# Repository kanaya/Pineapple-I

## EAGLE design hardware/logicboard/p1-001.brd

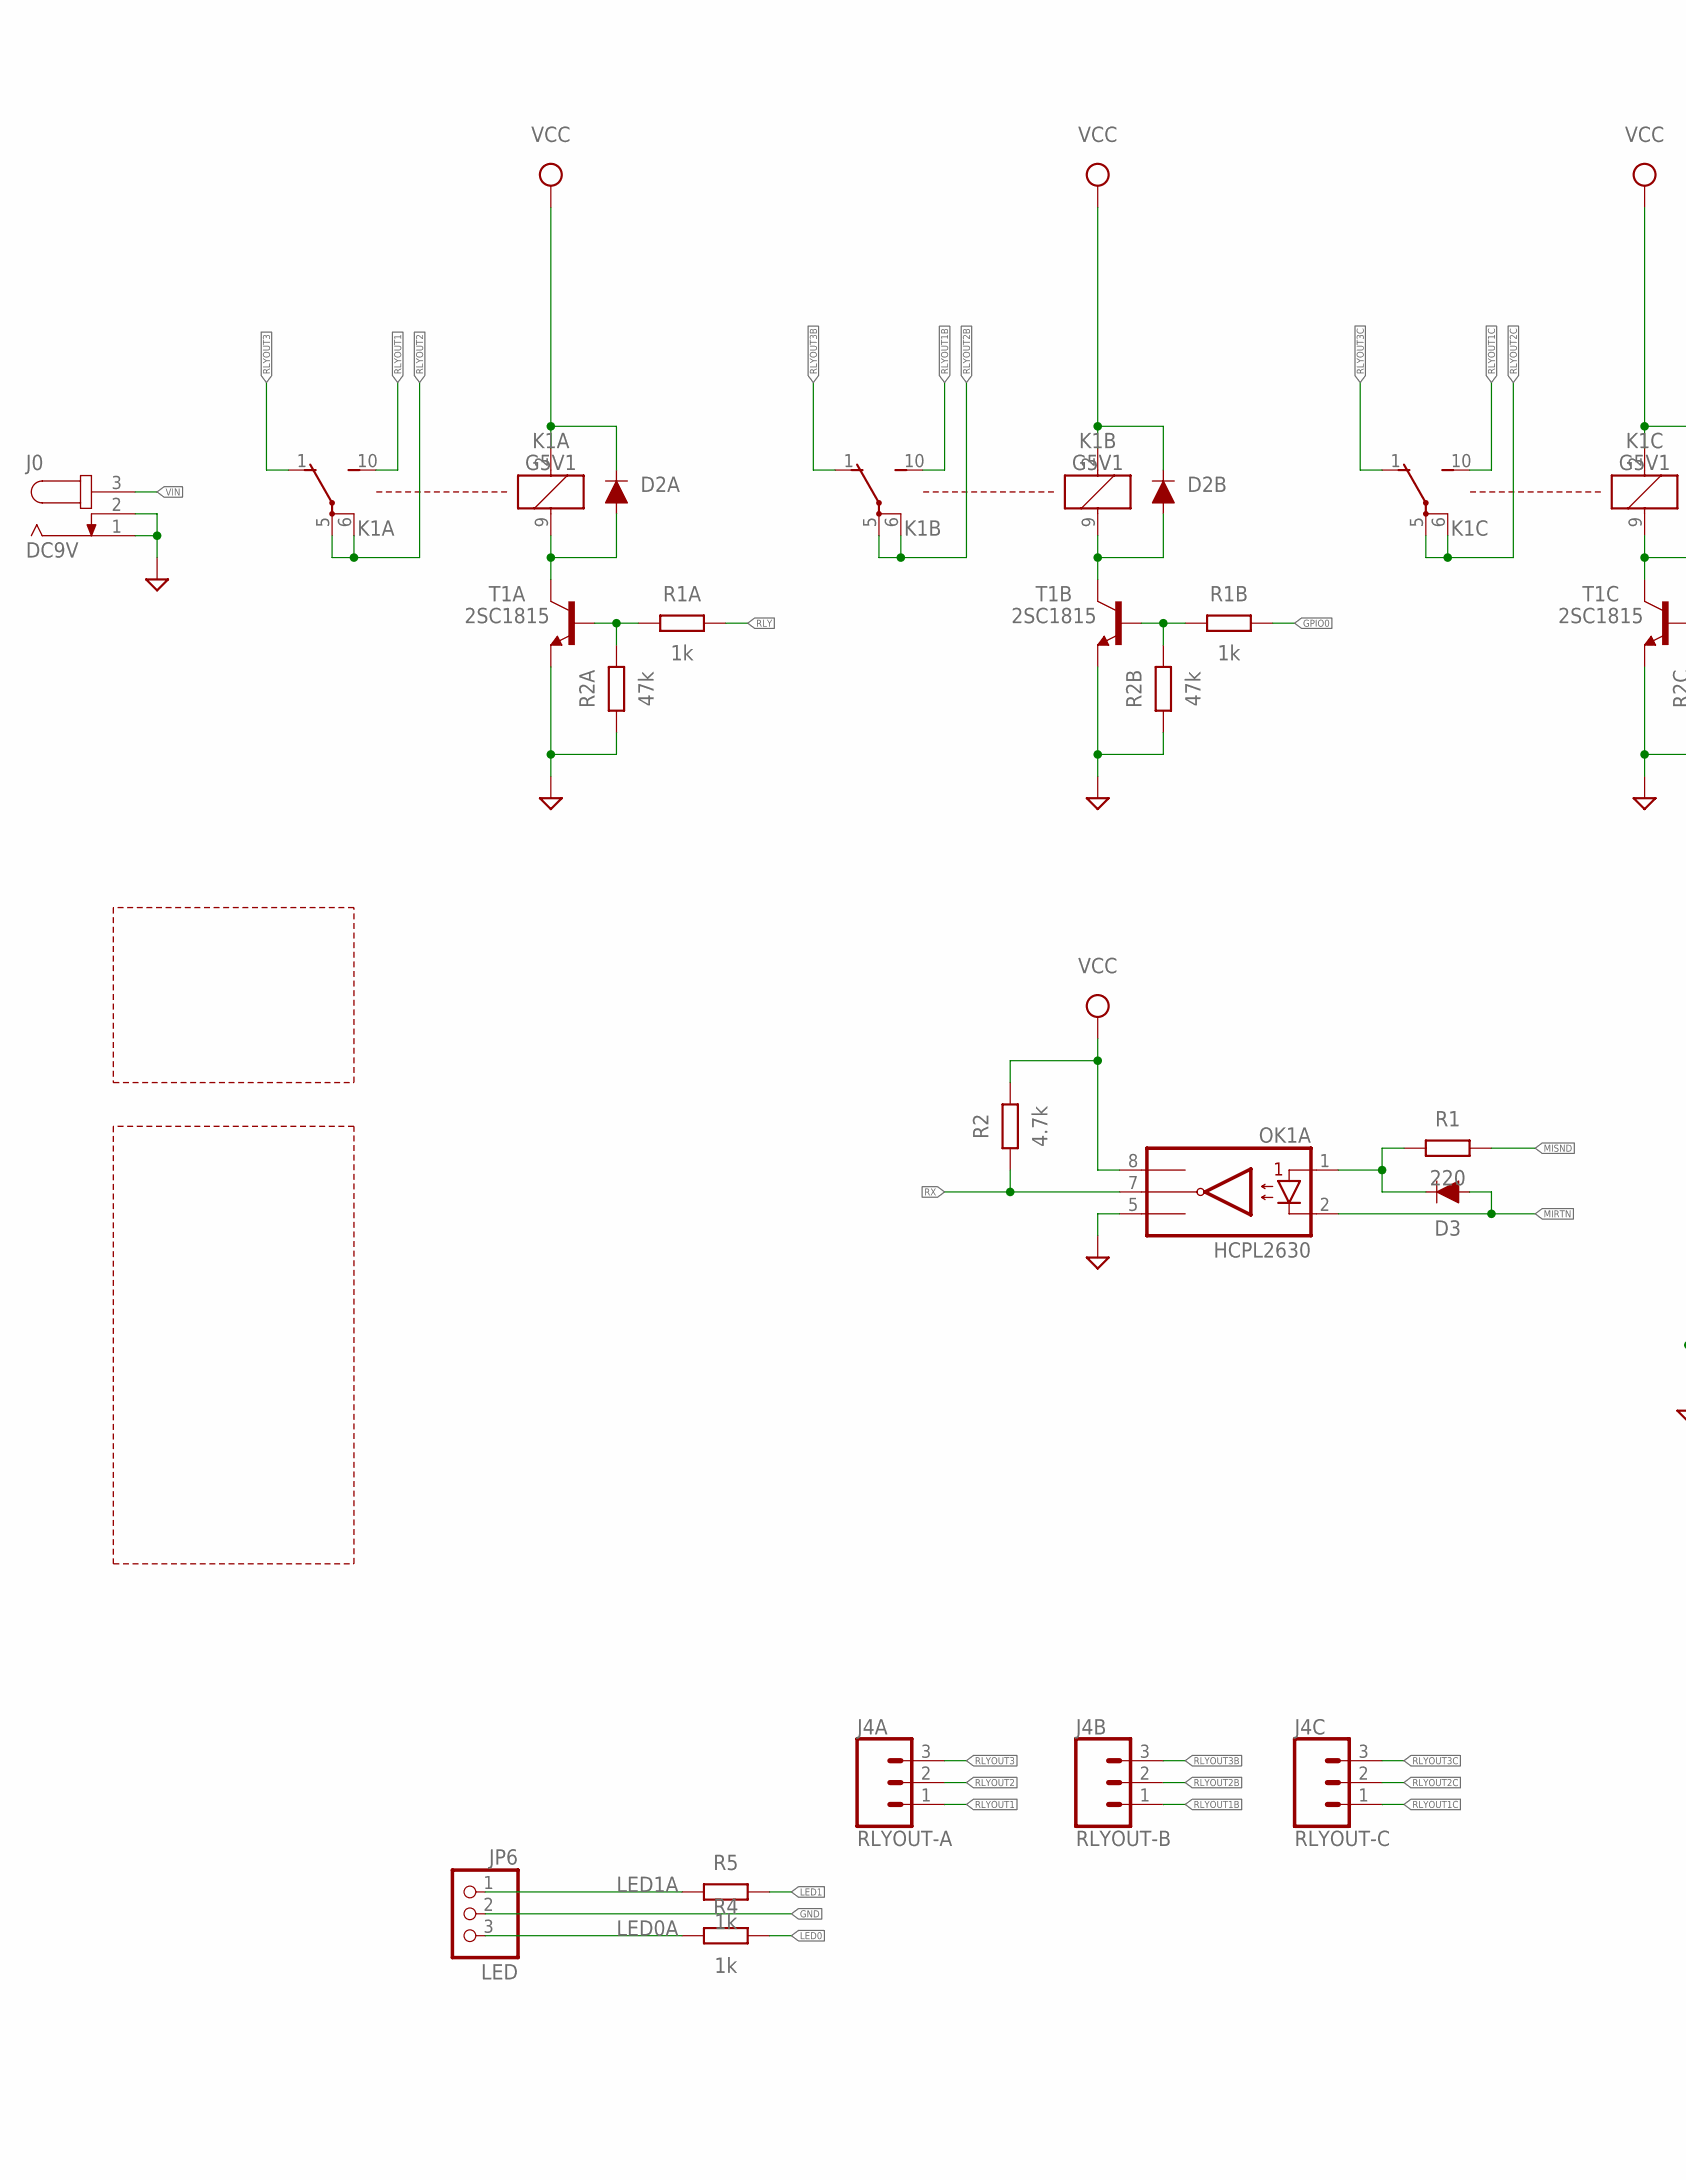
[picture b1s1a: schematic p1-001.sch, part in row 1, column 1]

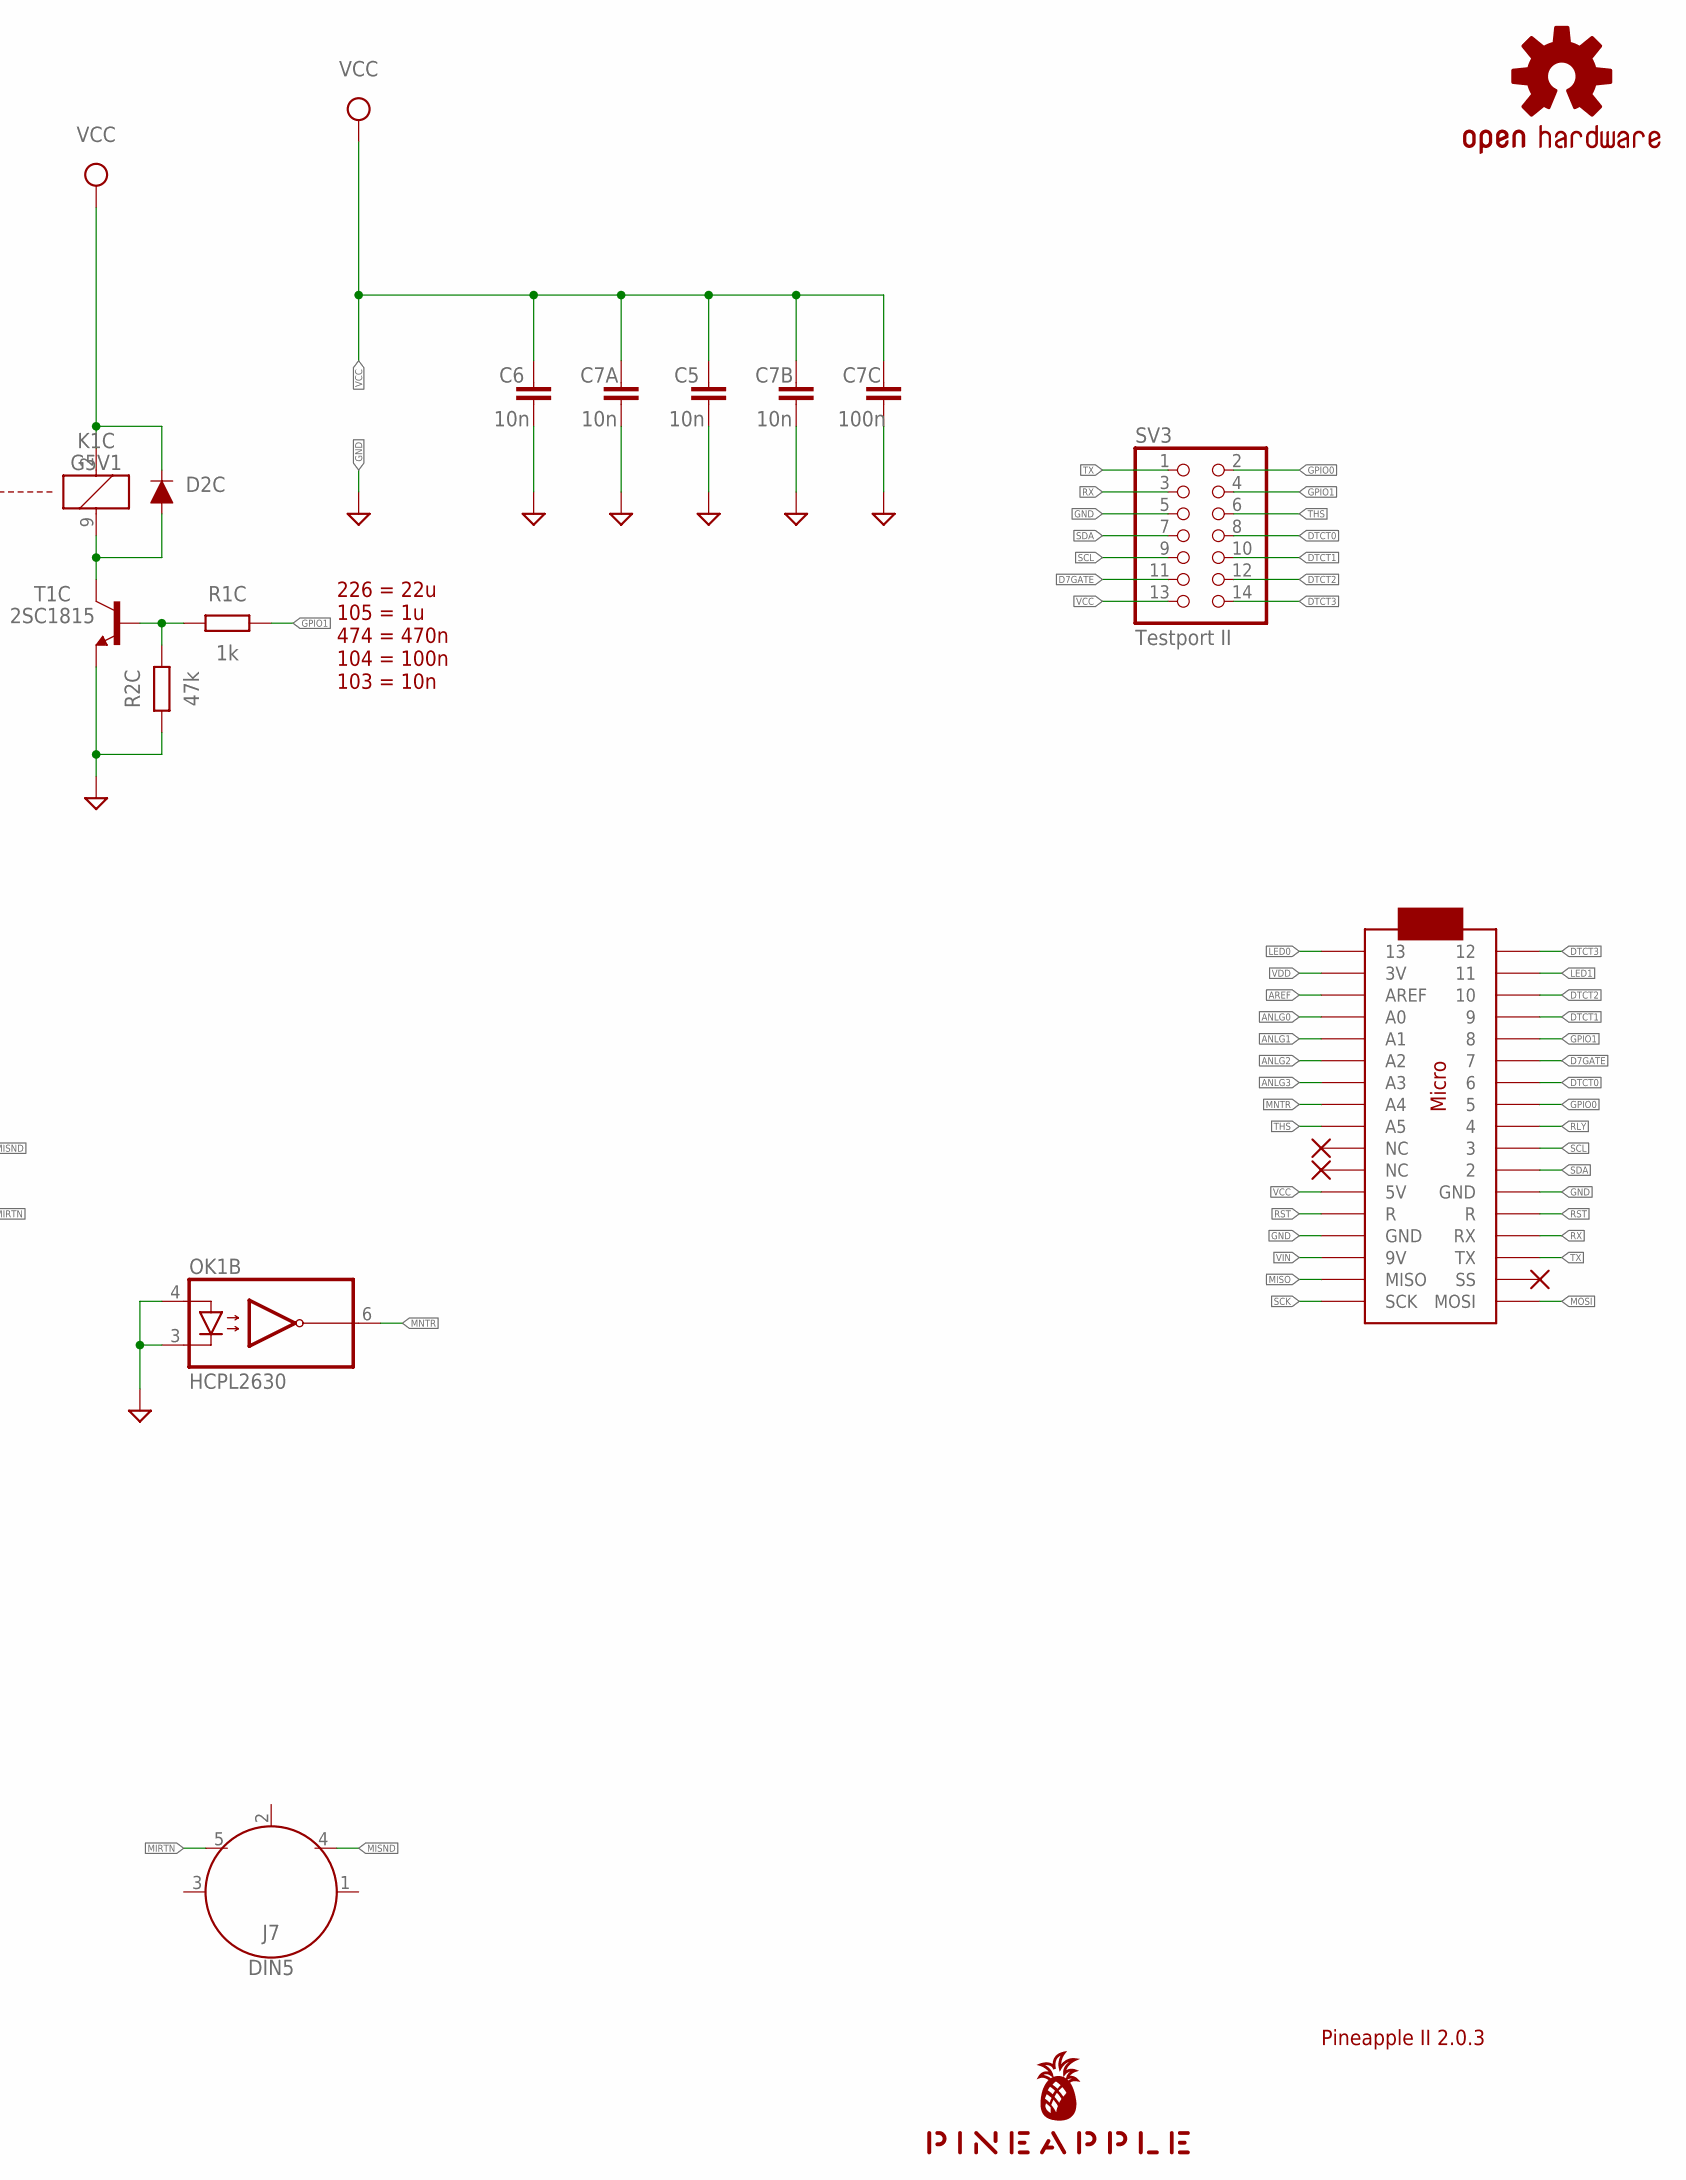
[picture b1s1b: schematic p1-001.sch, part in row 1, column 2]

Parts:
C5, C6, C7A, C7B: 10n; C025-024X044
C7C: 100n; C025-024X044
D2A, D2B, D2C, D3: DIODE-1N4148
J0: DC9V; SPC4077
J4A: RLYOUT-A; JST-3-PTH
J4B: RLYOUT-B; JST-3-PTH
J4C: RLYOUT-C; JST-3-PTH
J7: DIN5; DIN5-RA-PTH
JP6: LED; 1X03
K1A, K1B, K1C: G5V1
LOGO1: OSHW-LOGOS-COPPER; OSHW-LOGO-S_COPPER
MC1: ARDUINOMICRO
OK1: HCPL2630; DIL08
R1: 220; 0204/5
R1A, R1B, R1C, R4, R5: 1k; 0204/5
R2: 4.7k; 0204/5
R2A, R2B, R2C: 47k; 0204/5
SV3: Testport II; 2X07
T1A, T1B, T1C: 2SC1815; TO92-ECB
U$1: PINEAPPLE450_SILK

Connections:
ANLG0: MC1.P$31 (A0)
ANLG1: MC1.P$30 (A1)
ANLG2: MC1.P$29 (A2)
ANLG3: MC1.P$28 (A3)
AREF: MC1.P$32 (AREF)
D7GATE: MC1.P$6 (7), SV3.11; also elsewhere on the board
DTCT0: MC1.P$7 (6), SV3.8
DTCT1: MC1.P$4 (9), SV3.10
DTCT2: MC1.P$3 (10), SV3.12
DTCT3: MC1.P$1 (12), SV3.14
GND: C5.2, C6.2, C7A.2, C7B.2, C7C.2, J0.1, J0.2, JP6.2, MC1.P$12 (GND), MC1.P$21 (GND), OK1.3 (C2), OK1.4 (A2), OK1.5 (GND), R2A.1, R2B.1, R2C.1, SV3.5, T1A.E, T1B.E, T1C.E; also elsewhere on the board
GPIO0: MC1.P$8 (5), R1B.2, SV3.2; also elsewhere on the board
GPIO1: MC1.P$5 (8), R1C.2, SV3.4; also elsewhere on the board
LED0: MC1.P$34 (13), R4.2
LED0A: JP6.3, R4.1
LED1: MC1.P$2 (11), R5.2
LED1A: JP6.1, R5.1
MIDIINSND: D3.C, OK1.1 (A1), R1.1
MIRTN: D3.A, J7.5, OK1.2 (C1)
MISND: J7.4, R1.2
MISO: MC1.P$19 (MISO); also elsewhere on the board
MNTR: MC1.P$27 (A4), OK1.6 (VO2)
MOSI: MC1.P$17 (MOSI); also elsewhere on the board
RLY: MC1.P$9 (4), R1A.2
RLYDRV: R1A.1, R2A.2, T1A.B
RLYDRV1: R1B.1, R2B.2, T1B.B
RLYDRV2: R1C.1, R2C.2, T1C.B
RLYOUT1: J4A.1, K1A.10 (S)
RLYOUT1B: J4B.1, K1B.10 (S)
RLYOUT1C: J4C.1, K1C.10 (S)
RLYOUT2: J4A.2, K1A.5, K1A.6
RLYOUT2B: J4B.2, K1B.5, K1B.6
RLYOUT2C: J4C.2, K1C.5, K1C.6
RLYOUT3: J4A.3, K1A.1 (O)
RLYOUT3B: J4B.3, K1B.1 (O)
RLYOUT3C: J4C.3, K1C.1 (O)
RLYSNK: D2A.A, K1A.9 (2), T1A.C
RLYSNK1: D2B.A, K1B.9 (2), T1B.C
RLYSNK2: D2C.A, K1C.9 (2), T1C.C
RST: MC1.P$13 (R), MC1.P$22 (R); also elsewhere on the board
RX: MC1.P$14 (RX), OK1.7 (VO1), R2.1, SV3.3
SCK: MC1.P$18 (SCK); also elsewhere on the board
SCL: MC1.P$10 (3), SV3.9; also elsewhere on the board
SDA: MC1.P$11 (2), SV3.7; also elsewhere on the board
THS: MC1.P$26 (A5), SV3.6
TX: MC1.P$15 (TX), SV3.1
VCC: C5.1, C6.1, C7A.1, C7B.1, C7C.1, D2A.C, D2B.C, D2C.C, K1A.2 (1), K1B.2 (1), K1C.2 (1), MC1.P$23 (5V), OK1.8 (VCC), R2.2, SV3.13; also elsewhere on the board
VDD: MC1.P$33 (3V)
VIN: J0.3, MC1.P$20 (9V)

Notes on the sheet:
Pineapple II 2.0.3
226 = 22u 105 = 1u 474 = 470n 104 = 100n 103 = 10n

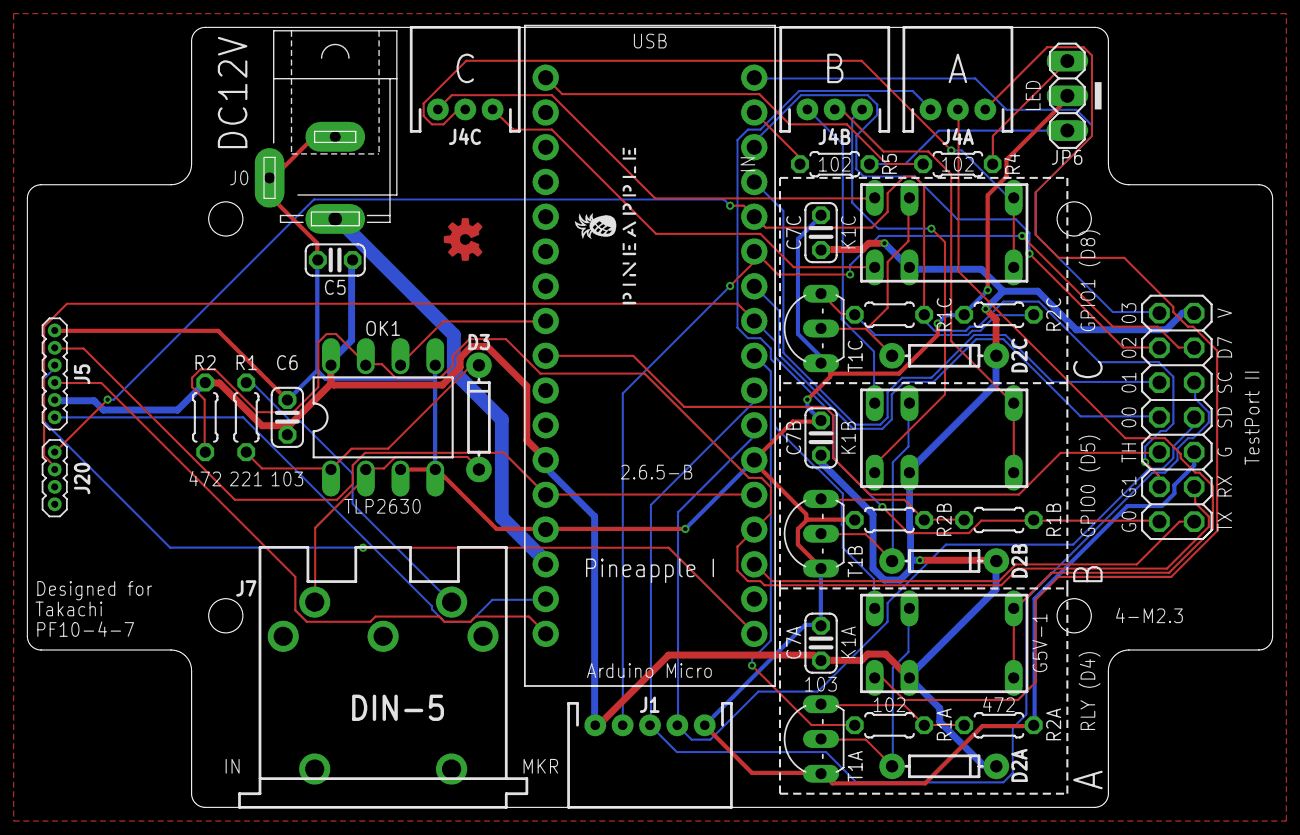
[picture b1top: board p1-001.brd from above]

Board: 2 copper layers, 91.0 x 57.0 mm, 39 parts (0 on the bottom side), 43 nets.

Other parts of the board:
J1: JST-5-PTH
J5: 1X06_1.27MM
J20: 1X04_1.27MM

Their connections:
D7GATE: J1.4; also elsewhere on the board
GND: J1.1, J5.6; also elsewhere on the board
GPIO0: J20.3; also elsewhere on the board
GPIO1: J20.4; also elsewhere on the board
MISO: J5.1; also elsewhere on the board
MOSI: J5.4; also elsewhere on the board
RST: J5.5; also elsewhere on the board
SCK: J5.3; also elsewhere on the board
SCL: J1.3; also elsewhere on the board
SDA: J1.2; also elsewhere on the board
VCC: J1.5, J5.2; also elsewhere on the board

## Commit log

2022-08-01 Imported schematic and board design from Pineapple Zero 2.0.
2022-08-01 File rename.
2022-08-01 Copied Pineapple IIb 2.6.1 as P1.
2022-08-01 Removed many parts.
2022-08-01 3-pin relay port.
2022-08-02 Removed several parts.
2022-08-03 The first should-be-working model.
2022-08-03 Autorouted.
2022-08-03 Silk.
2022-08-03 GND pattern. Dimension check.
2022-08-03 Removed test files.
2022-08-03 Fixed signaling error.
2022-08-03 FusionPCB package.
2022-09-17 J1, J5, and J20.

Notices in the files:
parts and their libraries:
SparkFun-DiscreteSemi: Licensing: Creative Commons ShareAlike 4.0 International - https://creativecommons.org/licenses/by-sa/4.0
